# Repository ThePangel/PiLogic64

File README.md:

# PiLogic64 🎮✨

> An open-source logic puzzle console 
## What is this?

**PiLogic64** is a handheld logic puzzle gaming console powered by a Raspberry Pi Pico. This project brings interactive logic puzzles and games to makers everywhere—at a fraction of the cost and with infinite customizability.

### Features 🚀

- **8x8 NeoPixel Matrix Display** - Bright, colorful LED matrix for puzzle visualization
- **OLED Screen** - Navigate menus and game selection with ease
- **Dual Rotary Encoders** - Intuitive controller input for puzzle solving
- **Audio Output** - Up to dual speakers for satisfying sound effects and feedback
- **SD Card Support** - Easily add new puzzles and games by dropping files on an SD card
- **Rechargeable Power** - 2 18650 Li-ion battery with TP4056 charging circuit and MT3608 buck converter for stable 5V power
- **100% Open Source** - PCB designs, schematics, and code available for the community

### Tech Specs 🔧

- **Microcontroller**: Raspberry Pi Pico (or Pico 2)
- **Display**: 8x8 NeoPixel Matrix + OLED
- **Power**: 2 18650 cells (3.7V) → TP4056 charger → MT3608 boost to 5V
- **Audio**: PAM8403 amplifier
- **Input**: 2x Rotary Encoders
- **Storage**: SD Card slot

## Game Examples 🎯

Here are some games I have thought for the PiLogic64!
(Some I will code myself, but feel free to make any of these!)

### Logic Puzzles
- **Mastermind** - Crack the color code using logic and deduction
- **Color Sudoku** - 8x8 Sudoku with colored LEDs instead of numbers
- **Lights Out** - Toggle lights to turn them all off in a cascading puzzle
- **Pattern Memory** - Simon-style memory game with increasing sequences
- **Minesweeper** - Classic logic game adapted for the LED matrix

### Action Games
- **Snake** - Classic snake game with colorful trails
- **Tetris Mini** - Block-stacking puzzle on a compact grid

### Creative Puzzles

- **Color Match** - Pattern matching and replication challenges
- **Logic Gates** - Educational puzzles teaching boolean logic

*...and infinitely more! Just code and drop new game files on the SD card.*

## Development Journey 📔

This project is being documented on [Hack Club Blueprint](https://blueprint.hackclub.com/projects/380). Check it out for detailed build logs, photos, and the full story!

## Credit
-   Footprints
    - [MT3608](https://github.com/kubabuda/misc_footprints/)
    -   [TP4056](https://github.com/ccadic/TP4056-18650) (I did modify this one)
    -   [PAM8403](https://github.com/johnnycubides/pam8403-module-kicad-lib/tree/main) (I did modify this one)
    -   [BK-18650-PC4](https://www.snapeda.com/parts/BK-18650-PC4/Memory%20Protection%20Devices/view-part/?p=BK-18650-PC2&welcome=home&ref=mpd_rel&t=None)

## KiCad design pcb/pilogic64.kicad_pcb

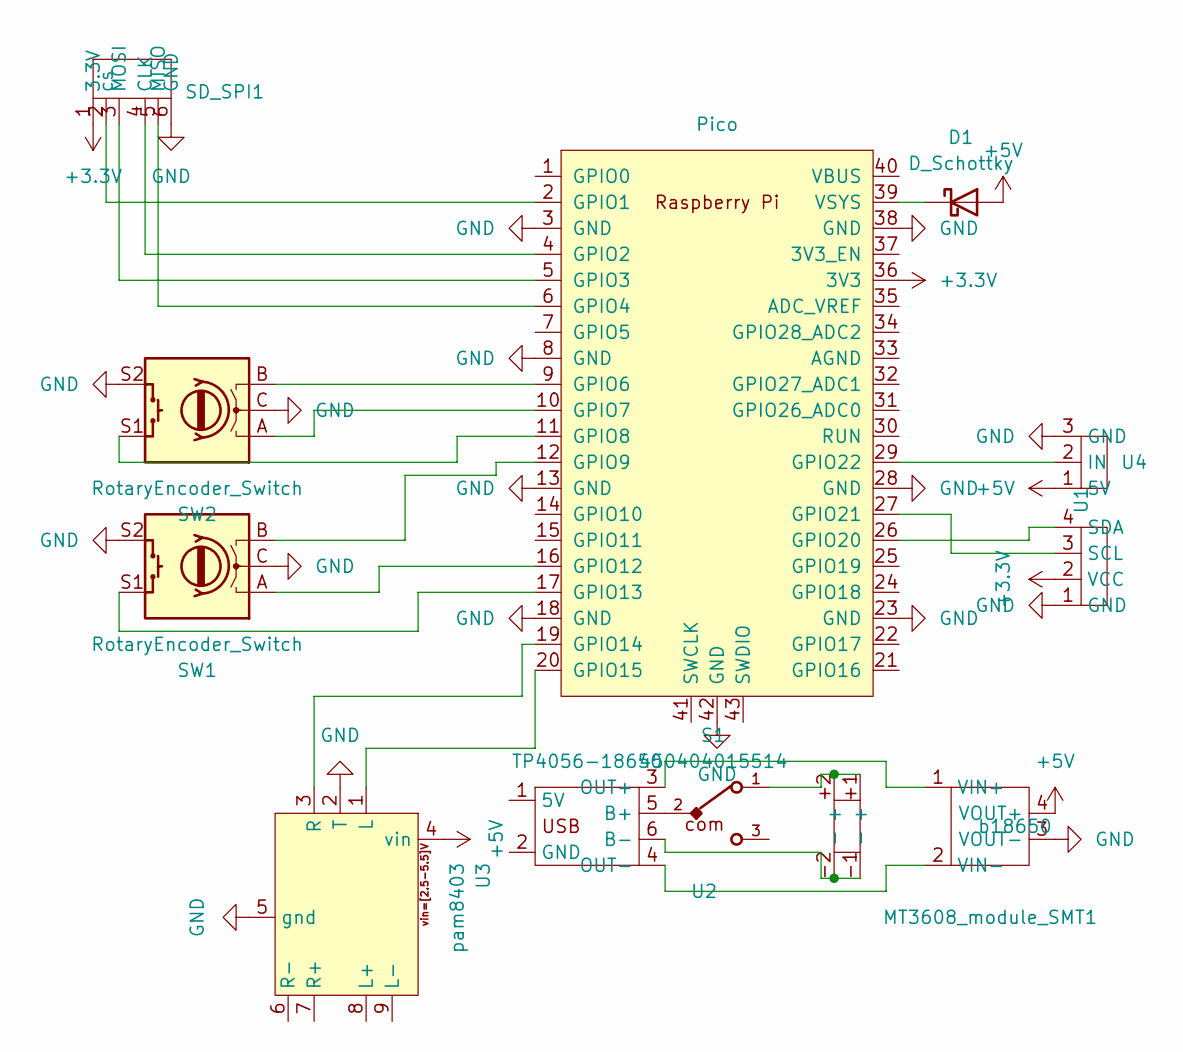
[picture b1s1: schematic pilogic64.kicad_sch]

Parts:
D1: D_Schottky; D_DO-41_SOD81_P10.16mm_Horizontal
MT3608_module_SMT1: MT3608_module_SMT
S1: 450404015514
SD_SPI1: PinHeader_1x06_P2.54mm_Vertical
SW1, SW2: RotaryEncoder_Switch; RotaryEncoder_Alps_EC11E-Switch_Vertical_H20mm
TP4056-18650: TP4056-18650
U1: PinHeader_1x04_P2.54mm_Vertical
U2: Pico; RPi_Pico_SMD_TH
U3: pam8403
U4: 8x8 MAtrix
b18650: 18650-PC4

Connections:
+3.3V: SD_SPI1.1 (3.3V), U1.2 (VCC), U2.36 (3V3)
+5V: D1.2 (A), MT3608_module_SMT1.4 (VOUT+), U3.4 (vin), U4.1 (5V)
GND: MT3608_module_SMT1.3 (VOUT-), S1.Z1, S1.Z2, S1.Z3, S1.Z4, SD_SPI1.6 (GND), SW1.C, SW1.MP, SW1.S2, SW2.C, SW2.MP, SW2.S2, U1.1 (GND), U2.3 (GND), U2.8 (GND), U2.13 (GND), U2.18 (GND), U2.23 (GND), U2.28 (GND), U2.38 (GND), U2.42 (GND), U3.2 (T), U3.5 (gnd), U4.3 (GND)
unnamed: D1.1 (K), U2.39 (VSYS)
unnamed: MT3608_module_SMT1.1 (VIN+), TP4056-18650.3 (OUT+)
unnamed: MT3608_module_SMT1.2 (VIN-), TP4056-18650.4 (OUT-)
unnamed: S1.1, b18650.+1 (+), b18650.+2 (+)
unnamed: SD_SPI1.4 (CLK), U2.4 (GPIO2)
unnamed: SD_SPI1.5 (MISO), U2.6 (GPIO4)
unnamed: SD_SPI1.3 (MOSI), U2.5 (GPIO3)
unnamed: SD_SPI1.2 (cs), U2.2 (GPIO1)
unnamed: S1.2, TP4056-18650.5 (B+)
unnamed: TP4056-18650.6 (B-), b18650.-1 (-), b18650.-2 (-)
unnamed: U1.3 (SCL), U2.27 (GPIO21)
unnamed: U1.4 (SDA), U2.26 (GPIO20)
unnamed: SW2.B, U2.9 (GPIO6)
unnamed: SW2.A, U2.10 (GPIO7)
unnamed: SW2.S1, U2.11 (GPIO8)
unnamed: SW1.B, U2.12 (GPIO9)
unnamed: SW1.A, U2.16 (GPIO12)
unnamed: SW1.S1, U2.17 (GPIO13)
unnamed: U2.19 (GPIO14), U3.3 (R)
unnamed: U2.20 (GPIO15), U3.1 (L)
unnamed: U2.29 (GPIO22), U4.2 (IN)

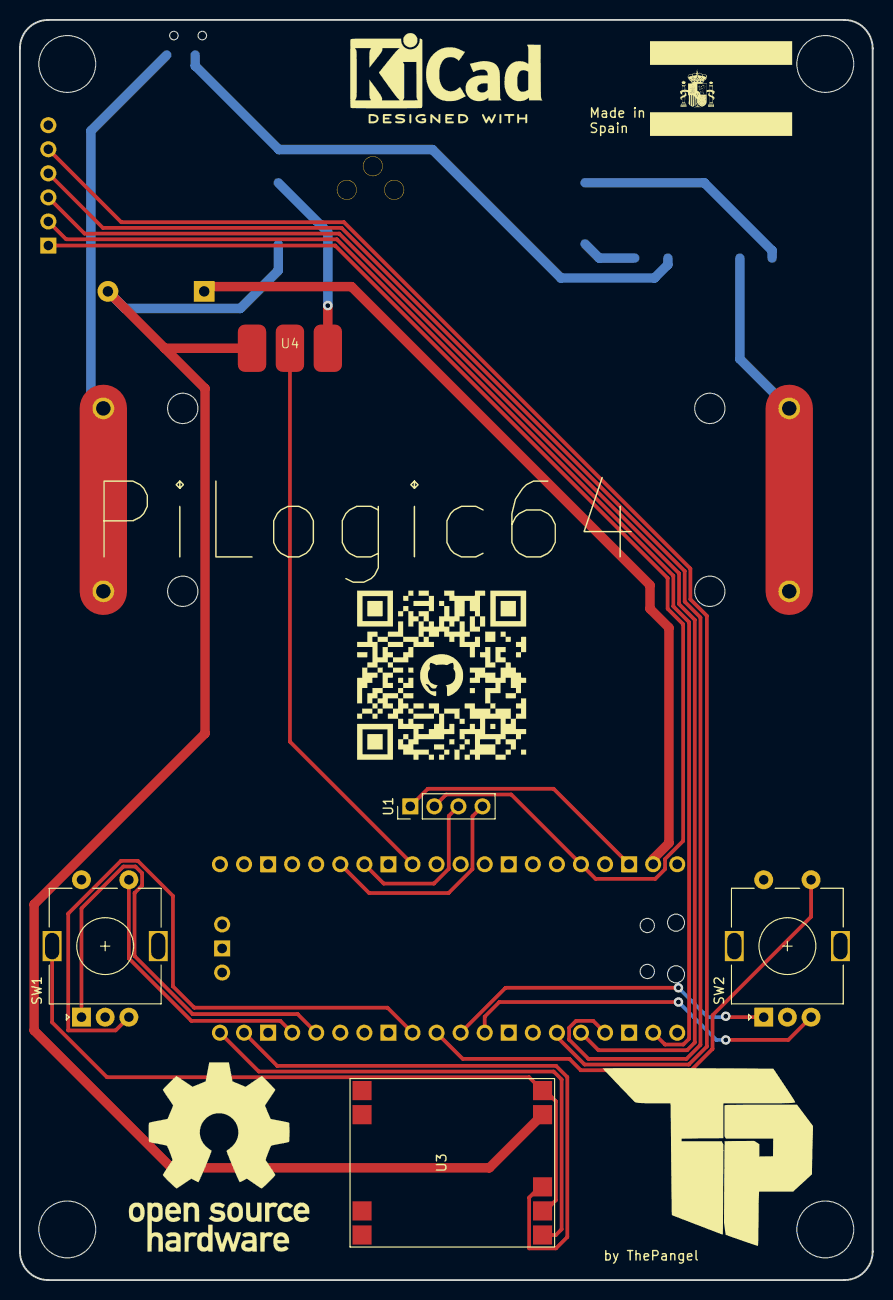
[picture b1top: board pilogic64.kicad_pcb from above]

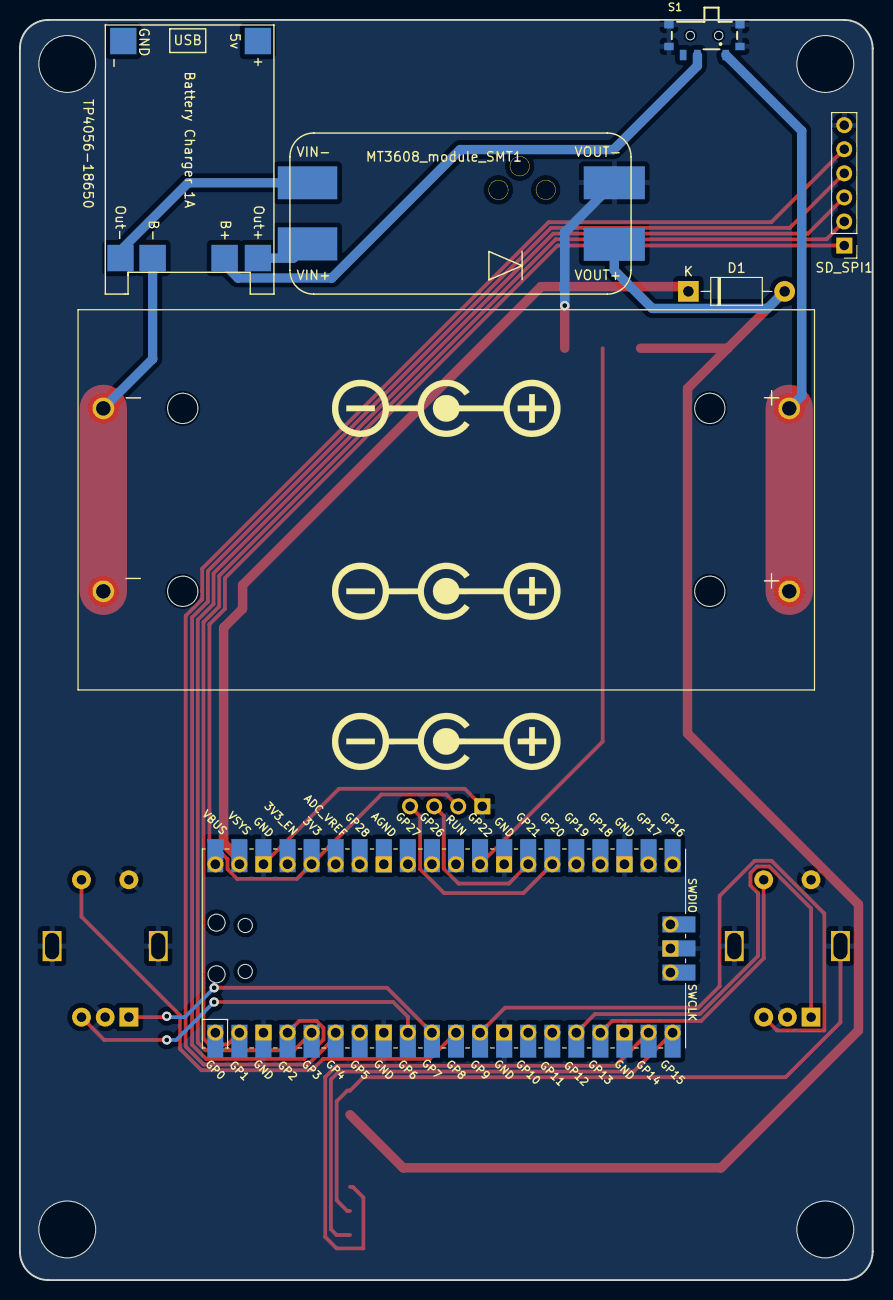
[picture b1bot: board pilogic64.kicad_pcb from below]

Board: 2 copper layers, 90.0 x 133.0 mm, 12 parts (7 on the bottom side), 24 nets.

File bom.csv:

"Id";"Designator";"Footprint";"Quantity";"Designation";"Supplier and ref";"Unit Price (€)";"Total Price (€)"
1;"LED1";"WS2812_8x8_Matrix";1;"WS2812 LED 5050 8X8 LED MATRIX";"AliExpress";"2.25";"2.25"
2;"SP1,SP2";"Speaker_2809";2;"2809 SPEAKER";"AliExpress";"2.27";"5.35"
3;"D1";"D_DO-41_SOD81_P10.16mm_Horizontal";1;"1N5817 DIODE";"AliExpress";"0.2";"1.36"
4;"BT1";"18650_Dual_Holder";1;"18650 DUAL BATTERY HOLDER";"AliExpress";"1.71";"1.71"
5;"U3";"PAM8403_Module";1;"PAM8403 MODULE";"AliExpress";"0.46";"1.38"
6;"SW1,SW2";"RotaryEncoder_Alps_EC11E-Switch_Vertical_H20mm";2;"EC11 ENCODER";"AliExpress";"1.21";"2.43"
7;"OLED1";"OLED_0.96_I2C";1;"0.96 INCH OLED I2C";"AliExpress";"1.99";"1.99"
8;"U4";"MT3608_Module";1;"MT3608 MODULE";"AliExpress";"0.74";"1.48"
9;"SD1";"MicroSD_Reader";1;"MICRO SD CARD READER";"AliExpress";"0.80";"0.80"
10;"U5";"TP4056_Module";1;"TP4056 MODULE";"AliExpress";"0.34";"1.71"
11;"U1";"RPi_Pico2_SMD_TH";1;"RASPBERRY PI PICO 2";"AliExpress";"5.69";"5.69"
12;"BAT";"18650";2;"18650";"AliExpress";"3.18";"6.26"
13;"PCB1";"Custom_PCB";1;"CUSTOM PCB (shipping included)";"JLCPCB";"30.10";"30.10"

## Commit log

2025-10-11 Initial structure plus some pcb stuff
2025-10-11 Added credits
2025-10-11 Fixed symbols plus other changes
2025-10-11 More pcb!
2025-10-12 Finished cicuit, and I think also finished pcb
2025-10-12 Add credits
2025-10-13 added 3d models and some pcb tweaks
2025-10-13 Finished PCB, added BOM
2025-10-13 Add BOM file for components used in the project
2025-10-13 Update BOM file with supplier and pricing information
2025-10-13 Edit BOM file
2025-11-06 Add new symbols for components and remove lock files; implement main functionality for game selection on microcontroller
